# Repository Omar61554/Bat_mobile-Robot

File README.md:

<h1 align="center" id="title">Bat_mobile-Robot</h1>

## MCT131s Introduction to Mechatronics Project Fall2023

### Abstract
design and manufacture a bat-mobile robot that follows the black line using IR sensors and implements some missions identified by a color sensor  using a specially designed shooting mechanism.  

### Mind Map

<h4 align="center" id="title">light Mode</h4>     

### Modules
● **Navigation:** All the functions for line following and color sensor 

● **Shooting:** Functions for selecting the ball and shooting it

● **Bluetooth:** Communication between the robot and the bat cave

### System

[schematicV1.0.PDF](https://github.com/Omar61554/Bat_mobile-Robot/files/13831259/schematicV1.0.PDF)

the system consists of 2 arduinos, master and slave communicating with UART protocol sending signals from the color sensor of the mission color and received by the slave to start the shooting and then reply at the end of the mission.

#### PCB

## CAD

## Robot

## Video
Drive Link: https://drive.google.com/file/d/1enW-B_CkR1MSIdujXu7DNX1wD6lZzzd0/view?usp=share_link 
## Report
[Final Project Report-Team 9-Section2.pdf](https://github.com/Omar61554/Bat_mobile-Robot/files/13835303/Final.Project.Report-Team.9-Section2.pdf)

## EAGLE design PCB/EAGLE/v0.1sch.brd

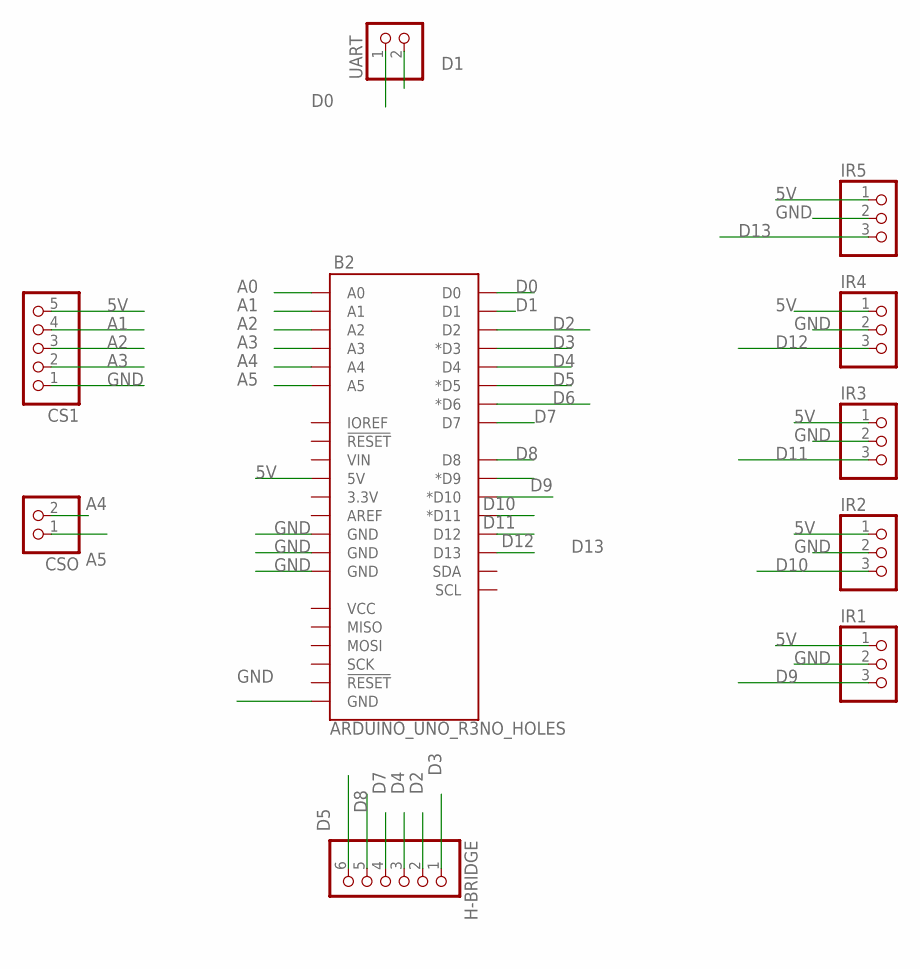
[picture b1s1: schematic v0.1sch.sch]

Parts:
B2: ARDUINO_UNO_R3NO_HOLES; ARDUINO_R3_NO_HOLES
CS1: PINHD-1X5; 1X05
CSO: PINHD-1X2; 1X02
H-BRIDGE: PINHD-1X6; 1X06
IR1, IR2, IR3, IR4, IR5: PINHD-1X3; 1X03
UART: PINHD-1X2; 1X02

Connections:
5V: B2.5V, CS1.5, IR1.1, IR2.1, IR3.1, IR4.1, IR5.1
A0: B2.A0
A1: B2.A1, CS1.4
A2: B2.A2, CS1.3
A3: B2.A3, CS1.2
A4: B2.A4, CSO.2
A5: B2.A5, CSO.1
D0: B2.D0, UART.1
D1: B2.D1, UART.2
D2: B2.D2, H-BRIDGE.2
D3: B2.D3 (*D3), H-BRIDGE.1
D4: B2.D4, H-BRIDGE.3
D5: B2.D5 (*D5), H-BRIDGE.6
D6: B2.D6 (*D6)
D7: B2.D7, H-BRIDGE.4
D8: B2.D8, H-BRIDGE.5
D9: B2.D9 (*D9), IR1.3
D10: B2.D10 (*D10), IR2.3
D11: B2.D11 (*D11), IR3.3
D12: B2.D12, IR4.3
D13: B2.D13, IR5.3
GND: B2.GND@1 (GND), B2.GND@2 (GND), B2.GND@3 (GND), B2.GND@4 (GND), CS1.1, IR1.2, IR2.2, IR3.2, IR4.2, IR5.2

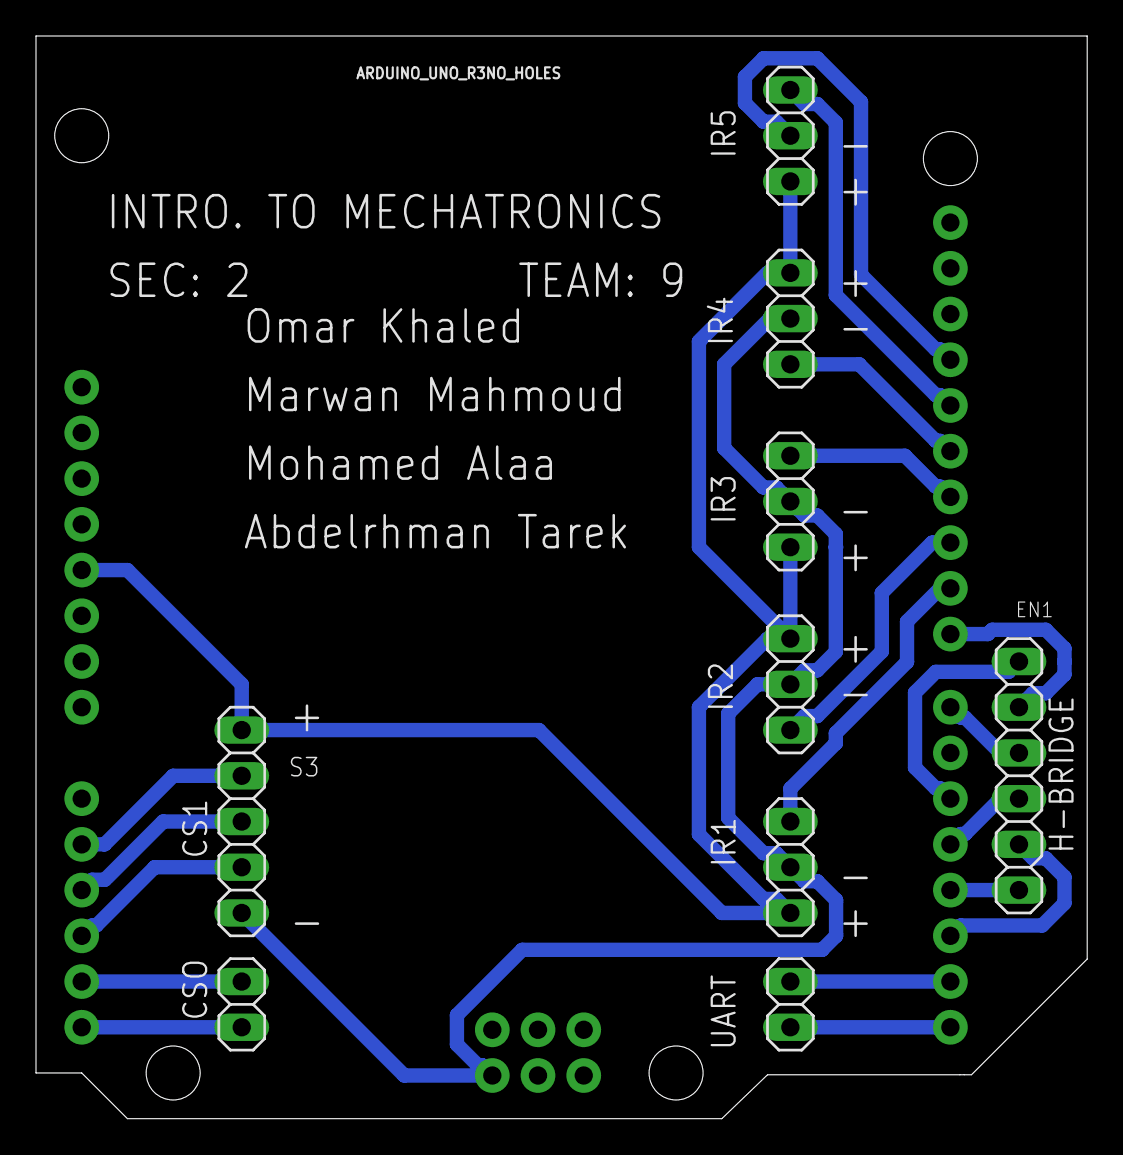
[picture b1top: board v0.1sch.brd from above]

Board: 2 copper layers, 58.4 x 60.1 mm, 10 parts (0 on the bottom side), 20 nets.

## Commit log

2023-10-25 obsidian
2023-10-25 init
2023-10-25 plan01
2023-10-25 test test test
2023-10-25 another test
2023-11-26 NAV-module
2023-12-01 color sensor
2023-12-06 Navigation
2023-12-06 colored schematic
2023-12-15 add 5 IR sensors
2023-12-16 add prototypes to interface file
2023-12-18 Reverse alg
2023-12-18 debug
2023-12-19 feat: add police chase mission
2023-12-21 feat: add car class
2023-12-21 feat: enhance class functions
2023-12-21 update the file
2023-12-21 enhance code
2023-12-23 add car class functions
2023-12-23 enhance police mission function
2023-12-24 feat: finalizing missions
2023-12-24 finalizing functions for testing
2023-12-24 small edit
2023-12-26 change arduino pins
2023-12-26 finalize pins
2023-12-27 major-update_V0.1
2023-12-27 add last changes
2023-12-27 add some comments
2023-12-27 add latest updates from master to program cpp
2023-12-27 add latest updates to nav interface h
2023-12-27 adding latest updates
2023-12-27 remove some comments
2023-12-27 update navigation cpp
2023-12-27 finish master code integeration
2023-12-27 moving slave file
2023-12-27 add bluetooth functions
2023-12-27 add interface file
2024-01-04 add latest changes
2024-01-04 Final

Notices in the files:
parts and their libraries:
SparkFun-Boards: Licensing: Creative Commons ShareAlike 4.0 International - https://creativecommons.org/licenses/by-sa/4.0
